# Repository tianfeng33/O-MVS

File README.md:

# O-MVS
The PCB designs for the Open MVS
These were made and released public in the hopes of promoting the simple, correct and safe consolitation of MVS systems and projects. 
This is V1.3 of the boards designed for the O-MVS project.  

These were designed using EASYEDA and I don't have a schematic specific for this design.
The KiCAD files were generated using https://wokwi.com/easyeda2kicad and have not be checked or tested for accuracy. 
They are meant for people to develop or modify so they can create derivative projects.

If you wish to use the project as is, please have boards made using the Gerbers or the files on OSH PARK. 
These have been tested thoroughly and I hold no responsibility for any damage to your MVS units or your equipment. 

Have fun and make some cool shit for the community.

TF

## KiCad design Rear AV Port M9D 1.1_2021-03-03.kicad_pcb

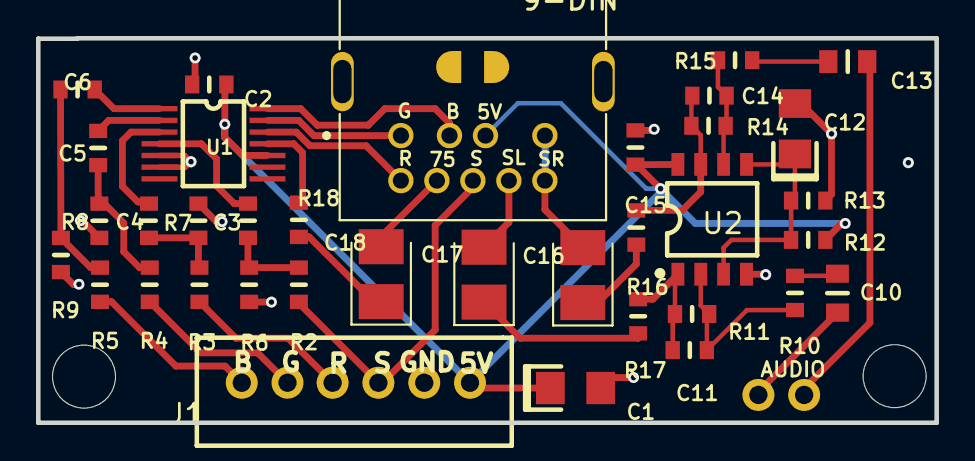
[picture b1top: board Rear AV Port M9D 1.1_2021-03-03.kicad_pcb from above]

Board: 2 copper layers, 49.9 x 21.4 mm, 39 parts (0 on the bottom side), 15 nets.

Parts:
9-DIN: MD-90SM; CUI_MD-90SM
AUDIO: JST 2.5
C1, C12: 22uF/10V; 1206_P
C2, C15: 0.1uF/50V; 0603
C3, C4, C5, C6, C11, C14: 270pF/50V; 0603
C10, C13: 0805
C16, C17, C18: CP_TANTALUM_CASE-B_EIA-3528-21_REFLOW
J1: 6PIN_2.54_MM_JST_XHP_JST_CONNECTOR BRO COPY
R2, R3, R4, R5: 5.62k; 0603
R6, R7, R8, R9, R18: 1.00k; 0603
R10, R15: 6.19k; 0603
R11, R14: 162k; 0603
R12, R13: 10.0k; 0603
R16, R17: 332; 0603
U1: THS7374IPWR; TSSOP-14
U2: DMP-8
U5, U6: M3

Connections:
+5V: 9-DIN.2, C1.1, C2.1, C15.1, J1.1, R12.1, U1.10, U2.8
B-OUT: 9-DIN.1, U1.14
BLUE: C6.1, C6.2, J1.6, R5.1, R5.2, R9.2, U1.1
G-OUT: 9-DIN.3, U1.13
GND: 9-DIN.S1, 9-DIN.S2, 9-DIN.S3, C1.2, C2.2, C12.2, C15.2, J1.2, R6.1, R7.1, R8.1, R9.1, R13.1, U1.5, U1.6, U1.9, U2.4
GREEN: C5.1, C5.2, J1.5, R4.1, R4.2, R8.2, U1.2
LEFT: 9-DIN.8, AUDIO.3, C10.1, C10.2, C11.1, C11.2, C17.2, R10.1, R10.2, R11.1, R11.2, R17.2, U2.1, U2.2
R-OUT: 9-DIN.7, U1.12
RED: C4.1, C4.2, J1.4, R3.1, R3.2, R7.2, U1.3
RIGHT: 9-DIN.6, 9-DIN.9, AUDIO.4, C13.1, C13.2, C14.1, C14.2, C16.2, R14.1, R14.2, R15.1, R15.2, R16.1, U2.6, U2.7
SL: C17.1, R17.1
SR: C16.1, R16.2
SYNC: 9-DIN.5, C3.1, C3.2, J1.3, R2.1, R2.2, R6.2, U1.4
SYNC-75: 9-DIN.4, C18.1, C18.2, R18.1, R18.2, U1.11
VREF: C12.1, R12.2, R13.2, U2.3, U2.5

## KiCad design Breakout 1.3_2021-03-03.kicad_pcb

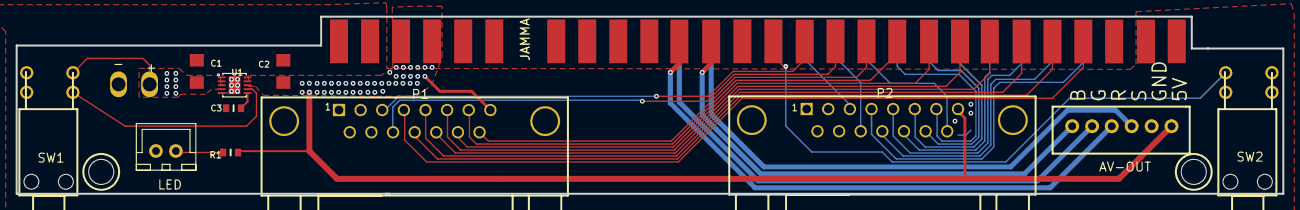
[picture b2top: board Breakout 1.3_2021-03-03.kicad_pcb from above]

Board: 2 copper layers, 161.7 x 22.6 mm, 15 parts (0 on the bottom side), 30 nets.

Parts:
+: 3.96MM 2P
C1, C2: R1206
C3: 0.1uF/50V; 0603
J1: 6PIN_2.54_MM_JST_XHP_JST_CONNECTOR BRO COPY
LED: JST_XH_2X2.54
P1, P2: Controller 1; DB15-M-DC
R1: 270pF/50V; 0603
SW1, SW2: PB400EEQR1BLK(CORRECT)
U1: EFUSE
U2, U5: M3 HOLE
U4: JAMMA SOLDER SIDE

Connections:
1PA: P1.13, U4.22
1PB: P1.5, U4.23
1PC: P1.12, U4.24
1PCOIN: P1.3, U4.16
1PD: P1.4, U4.25
1PDN: P1.7, U4.19
1PL: P1.14, U4.20
1PR: P1.6, U4.21
1PST: P1.11, U4.17
1PUP: P1.15, U4.18
2PA: P2.13, U4.Z
2PB: P2.5, U4._A
2PC: P2.12, U4._B
2PCOIN: P2.3, U4.T
2PD: P2.4, U4._C
2PDN: P2.7, U4.W
2PL: P2.14, U4.X
2PR: P2.6, U4.Y
2PST: P2.11, U4.U
2PUP: P2.15, U4.V
+5V: C2.1, J1.1, LED.1, P1.8, P2.8, R1.1, R1.2, U1.8, U1.9, U1.10, U4.3, U4.4, U4.C, U4.D
B: J1.6, U4.13
EN: SW1.4, U1.7
G: J1.5, U4.N
GND: +.1, C1.2, C2.2, C3.2, J1.2, LED.2, P1.0, P1.1, P2.0, P2.1, SW2.2, SW2.4, U1.5, U1.11, U4.1, U4.2, U4.27, U4.28, U4.A, U4.B, U4._E, U4._F
R: J1.4, U4.12
S: J1.3, U4.P
SST: C3.1, U1.6
TEST: SW2.1, U4.15
V-IN: +.2, C1.1, SW1.3, U1.1, U1.2, U1.3, U1.4

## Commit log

2021-05-26 Swapped out the op amp
    Decided to swap the audio op amp from the ne5532 to the opa1678.
2022-05-18 Slightly lowered the rgb voltage
    I slightly lowered the RGB voltage to account for different psu voltages with variances on the 5V. 1.4k changed to 1.33k
